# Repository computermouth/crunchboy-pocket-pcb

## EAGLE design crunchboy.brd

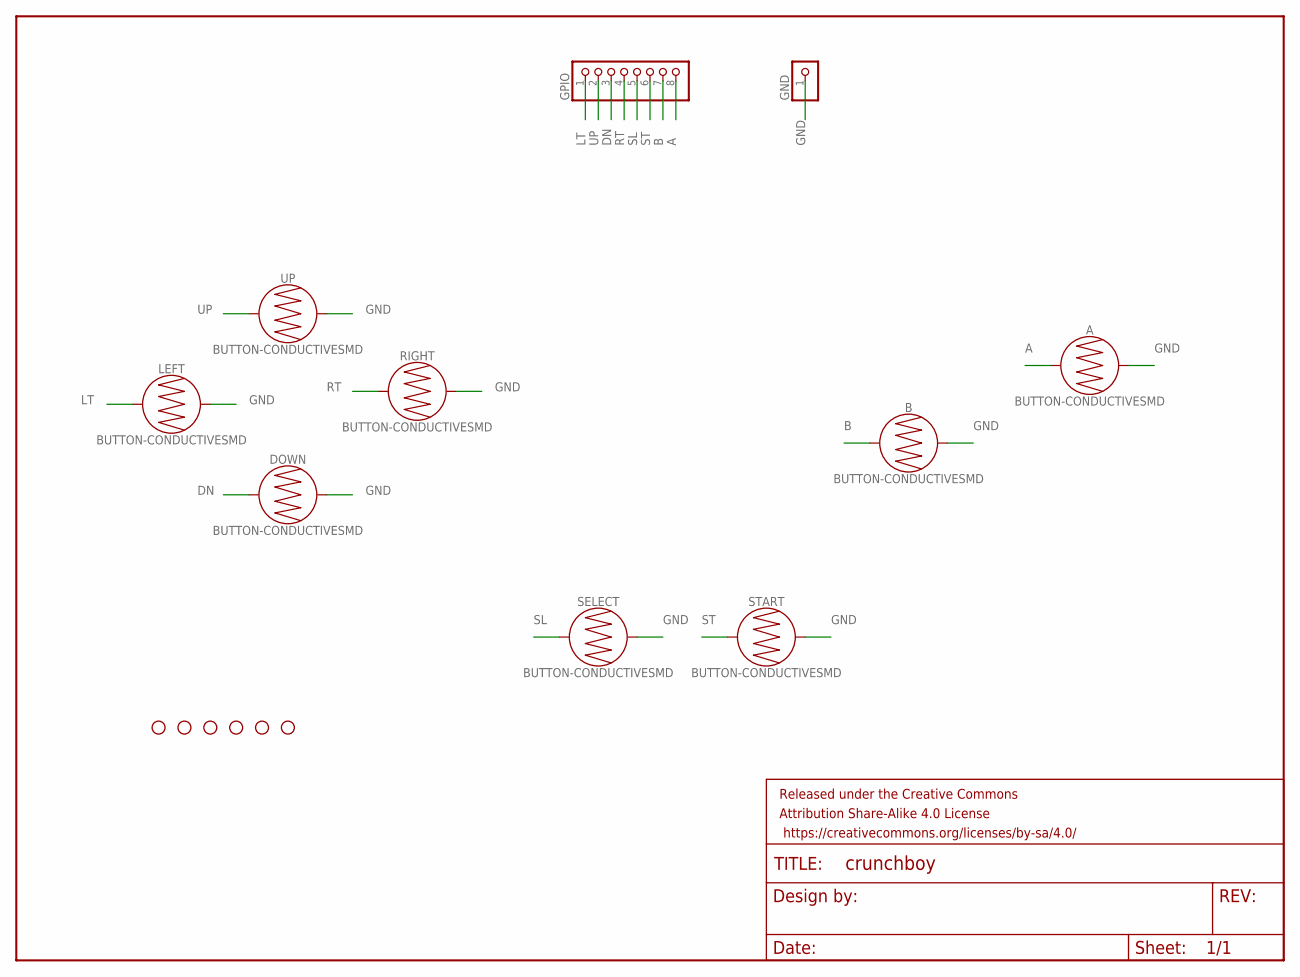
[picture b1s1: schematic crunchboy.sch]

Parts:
A: BUTTON-CONDUCTIVESMD; BUTTON-CONDUCTIVE
B: BUTTON-CONDUCTIVESMD; BUTTON-CONDUCTIVE
DOWN: BUTTON-CONDUCTIVESMD; BUTTON-CONDUCTIVE
FRAME1: FRAME-LETTER; CREATIVE_COMMONS
GND: PINHD-1X1; 1X01
GPIO: PINHD-1X8; 1X08
H10, H11, H12, H13, H15, H16: STAND-OFF
LEFT: BUTTON-CONDUCTIVESMD; BUTTON-CONDUCTIVE
RIGHT: BUTTON-CONDUCTIVESMD; BUTTON-CONDUCTIVE
SELECT: BUTTON-CONDUCTIVESMD; BUTTON-CONDUCTIVE
START: BUTTON-CONDUCTIVESMD; BUTTON-CONDUCTIVE
UP: BUTTON-CONDUCTIVESMD; BUTTON-CONDUCTIVE

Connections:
A: A.1, GPIO.8
B: B.1, GPIO.7
DN: DOWN.1, GPIO.3
GND: A.2, B.2, DOWN.2, GND.1, LEFT.2, RIGHT.2, SELECT.2, START.2, UP.2
LT: GPIO.1, LEFT.1
RT: GPIO.4, RIGHT.1
SL: GPIO.5, SELECT.1
ST: GPIO.6, START.1
UP: GPIO.2, UP.1

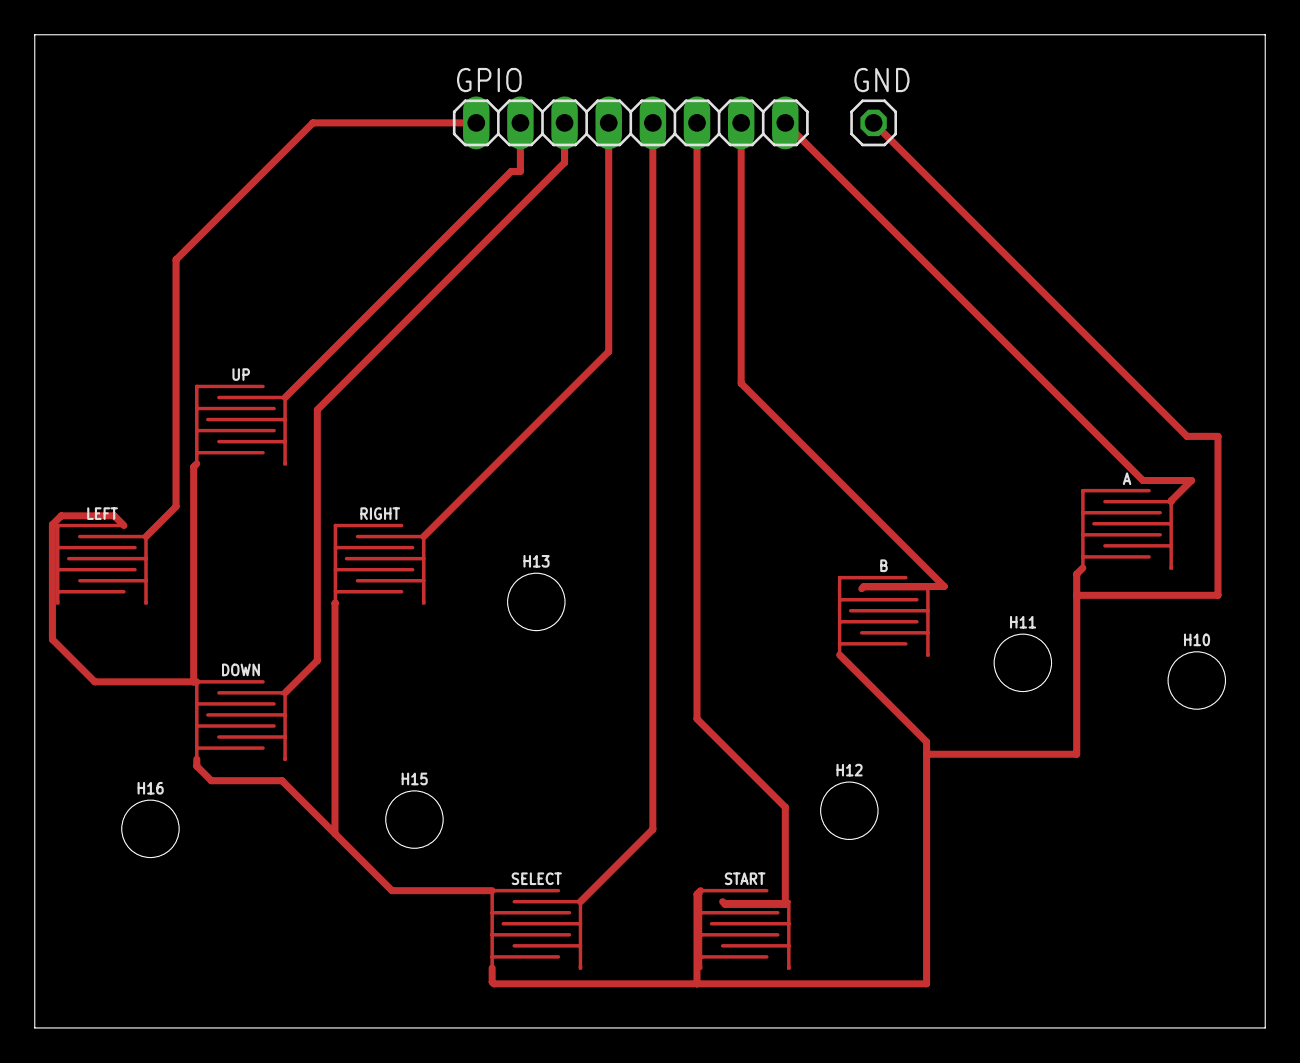
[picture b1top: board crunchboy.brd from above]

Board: 2 copper layers, 70.8 x 57.1 mm, 17 parts (0 on the bottom side), 9 nets.

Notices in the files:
parts and their libraries:
SparkFun-Switches: Licensing: Creative Commons ShareAlike 4.0 International - https://creativecommons.org/licenses/by-sa/4.0
SparkFun-Aesthetics: Released under the Creative Commons Attribution Share-Alike 4.0 License
SparkFun-Aesthetics: https://creativecommons.org/licenses/by-sa/4.0
